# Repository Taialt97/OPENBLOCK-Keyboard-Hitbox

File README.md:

>:warning: This project is currently under development; the PCBs have not been tested and may require additional optimization.

# Introduction
This project aims to create an open-source, modular, and easy-to-understand design for a Hit Box layout using the Raspberry Pi (RP2040) as the core. My goal is to make the project as accessible and customizable as possible, providing everyone with the flexibility to adapt the design to their specific needs.

## Chip Compatibility
- **GP2040 chip**: Offers higher compatibility with PC, PS4, PS3, Switch, and Xbox.

| ProMicro (Mega32U4) | RespbarryPie (GP2040) | NameOfSwitch | Action      | PlayStation   | Xbox   |
|---------------------|-----------------------|--------------|-------------|---------------|----------------|
| 6                   | 6                     | MX10         | Up         | Dpad Up   | Dpad Up             |            |                |
| 14                  | 20                    | MX2          | Down        |Dpad Down   | Dpad Down           |            |                |
| 16                  | 23                    | MX1          | Left        | Dpad Left   | Dpad Left           |            |                |
| 15                  | 22                    | MX3          | Right       | Dpad Right       | Dpad Right          |            |                |
| 21                  | 29                    | MX4          | Light Punch | Square        | X              |            |                |
| 5                   | 5                     | MX11         | Light Kick  | X             | A              |            |                |
| 4                   | 4                     | MX5          | Medium Punch| Circle        | B              |            |                |
| 20                  | 28                    | MX12         | Medium Kick | Triangle      | Y              |            |                |
| 18                  | 26                    | MX6          | Heavy Punch | L1            | LB             |            |                |
| 19                  | 27                    | MX13         | Heavy Kick  | R1            | RB             |            |                |
| 2                   | 2                     | MX7          | Triple Punch| L2            | LT             |            |                |
| 3                   | 3                     | MX14         | Triple Kick | R2            | RT             |            |                |
| 8                   | 8                     | MX8          | Select 1    | Select        | Back           |            |                |
| 7                   | 7                     | MX9          | Select 2    | Start         | Start          |            |                |

# Costs
The cost to build the fight-stick will depend on parts, shipping, and tools. Below is a breakdown:

1. PCB (minimum order of 5) without shipping: **$8**. Shipping will vary by location and method.
2. Parts for PCB assembly: **$25** (hot swap sockets, keys, switches, Pro Micro, and IC Sockets).
3. Tools: Varies widely, but a cost-effective approach is possible.

## Part List
### Micro Chips List
Below is a list of top-tier microcontrollers that I've found to be the best in the market. While more cost-effective alternatives are available from sites like Aliexpress (which I've personally tested and found satisfactory), the following options are slightly more expensive but come with a guarantee of proper functionality.

If you're using a different 12-pin microcontroller that you think should be included here, feel free to leave a comment!

1. [Elite-Pi - USB-C Pro Micro Replacement RP2040 Controller](https://keeb.io/collections/diy-parts/products/elite-pi-usb-c-pro-micro-replacement-rp2040)
2. [SparkFun Pro Micro - RP2040](https://www.sparkfun.com/products/18288)

### Parts List
To ensure affordability, I've listed essential parts and some alternatives:

- PCB | $8 (without shipping)
- (optional) Hot-swappable PCB socket | $3
- Keycaps | $5-$15 (depends on quality)
- Switch | $5-$50 (depends on the manufacturer and "quality" of the switch)
- Pro Micro | $4-$30 (ensure the chip is **RP2040**)

### Recommended
- KESTER SOLDER | $35-$60 (quality soldering wire)
- PINECIL – Smart Mini Portable Soldering Iron (Version 2) | $25.99-$35.99

# Code

Upon connecting the microcontroller to your computer, a new drive will appear. 
- Drag the `nuke.h` file into this drive; the microcontroller will disconnect and then reconnect.
- Drag the `OpenBlock.h` file into the drive. You'll hear a sound indicating that the drive has disconnected and reconnected.

To test your controller, visit the [Gamepad Tester Website](https://hardwaretester.com/gamepad).
For modifying the code or creating new code, go to the [GP2040-CE](https://gp2040-ce.info/#/) website.
There, you'll find all the resources you need to customize or create new code. If you have any questions, refer to our [Discord channel](https://discord.gg/kJDAZVwU) — they're awesome!

# Note
This project is an open-source initiative, designed for modularity and ease of understanding. Contributions and suggestions from the community are welcome, fostering collaboration and growth.

# Sponsorship
This repository is sponsored by [PCBWay](https://www.pcbway.com/).

PCBWay specializes in manufacturing high-quality PCBs. They offer a range of services including PCB prototyping, assembly, and much more. We are grateful for their support in making this project possible.
Simplify Your Custom PCB Orders with PCBWay

Ordering custom PCBs has never been easier, thanks to PCBWay's intuitive platform. With the 'Instant Quote' feature, you can swiftly enter crucial information such as PCB type, dimensions, and material. Plus, helpful tooltips and guides are there to assist you every step of the way.
Unmatched Verification Process

What sets PCBWay apart is their meticulous verification process. Once you upload your Gerber files, a team of experts scrutinizes them for any errors or omissions. You'll be promptly notified of any issues via email or directly on the platform, ensuring a nearly error-free process.
Real-Time Project Tracking

PCBWay takes your experience up a notch by offering real-time project tracking. This level of transparency allows you to better manage your project timelines and make well-informed decisions.
Reliable and Fast Shipping

When it's time to ship, PCBWay provides trustworthy options like DHL, FedEx, and OCS. Need it fast? Expedited shipping is available right from the get-go. In a recent test run, the entire process—from uploading the Gerber files to receiving the finished PCBs—took just six days.
Conclusion

PCBWay is a top choice for anyone transitioning from generic to custom PCBs. The platform excels in ease of use, quality control, and speed, making it ideal for specialized projects.
For more information, visit their [website](https://www.pcbway.com/).

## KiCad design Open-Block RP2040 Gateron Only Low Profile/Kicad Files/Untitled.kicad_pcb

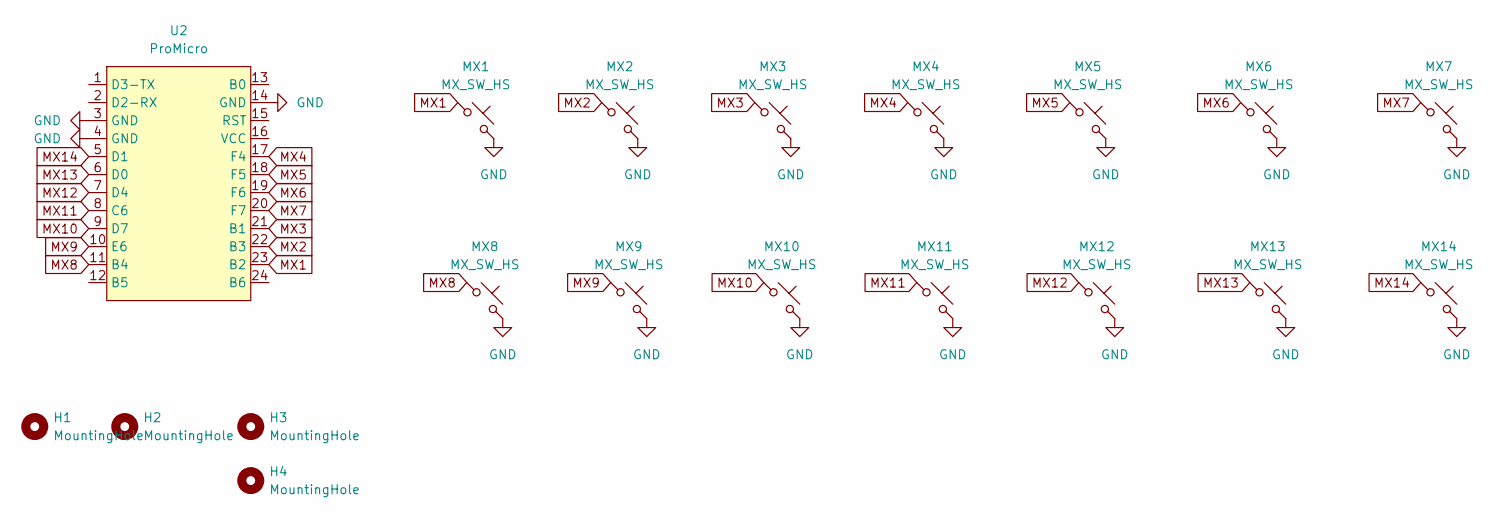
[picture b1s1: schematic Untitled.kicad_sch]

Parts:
H1, H2, H3, H4: MountingHole; MountingHole_2.2mm_M2_DIN965_Pad
MX1, MX2, MX3, MX4, MX5, MX6, MX7, MX8, MX9, MX10, MX11, MX12, MX13, MX14: MX_SW_HS; KAILHCHOK_V2_GATERON_SW_HS_(KAILH)
U2: ProMicro; Elite-C_ACH

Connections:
GND: MX1.2, MX2.2, MX3.2, MX4.2, MX5.2, MX6.2, MX7.2, MX8.2, MX9.2, MX10.2, MX11.2, MX12.2, MX13.2, MX14.2, U2.3 (GND), U2.4 (GND), U2.14 (GND)
MX1: MX1.1, U2.23 (B2)
MX2: MX2.1, U2.22 (B3)
MX3: MX3.1, U2.21 (B1)
MX4: MX4.1, U2.17 (F4)
MX5: MX5.1, U2.18 (F5)
MX6: MX6.1, U2.19 (F6)
MX7: MX7.1, U2.20 (F7)
MX8: MX8.1, U2.11 (B4)
MX9: MX9.1, U2.10 (E6)
MX10: MX10.1, U2.9 (D7)
MX11: MX11.1, U2.8 (C6)
MX12: MX12.1, U2.7 (D4)
MX13: MX13.1, U2.6 (D0)
MX14: MX14.1, U2.5 (D1)

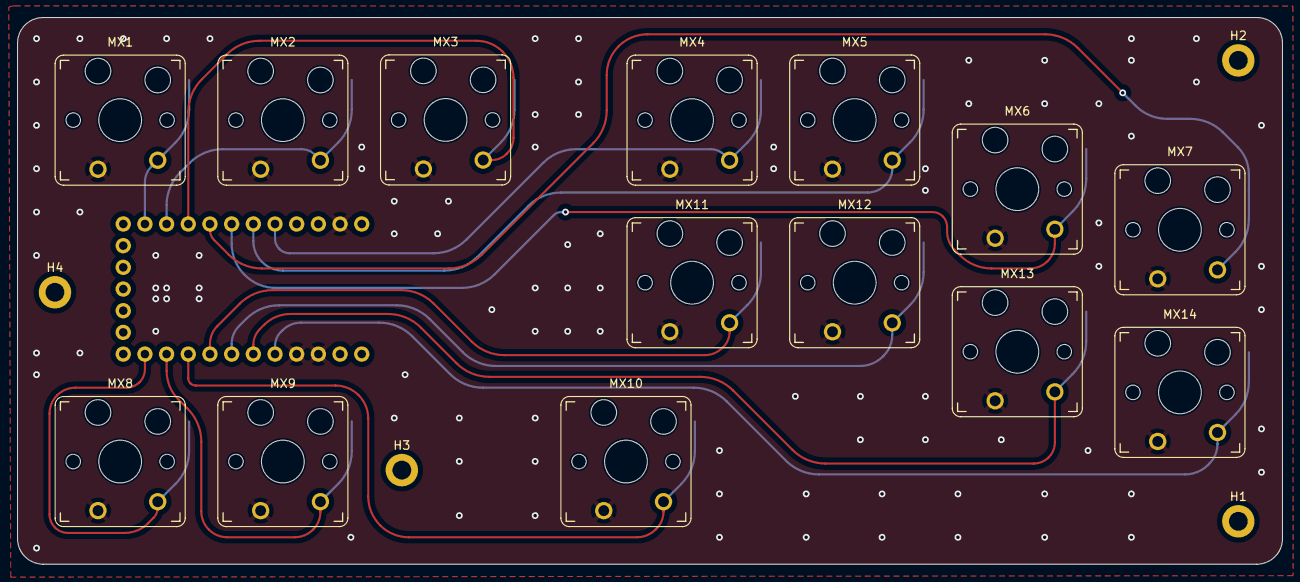
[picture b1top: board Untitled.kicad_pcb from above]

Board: 2 copper layers, 148.2 x 64.1 mm, 19 parts (1 on the bottom side), 15 nets.

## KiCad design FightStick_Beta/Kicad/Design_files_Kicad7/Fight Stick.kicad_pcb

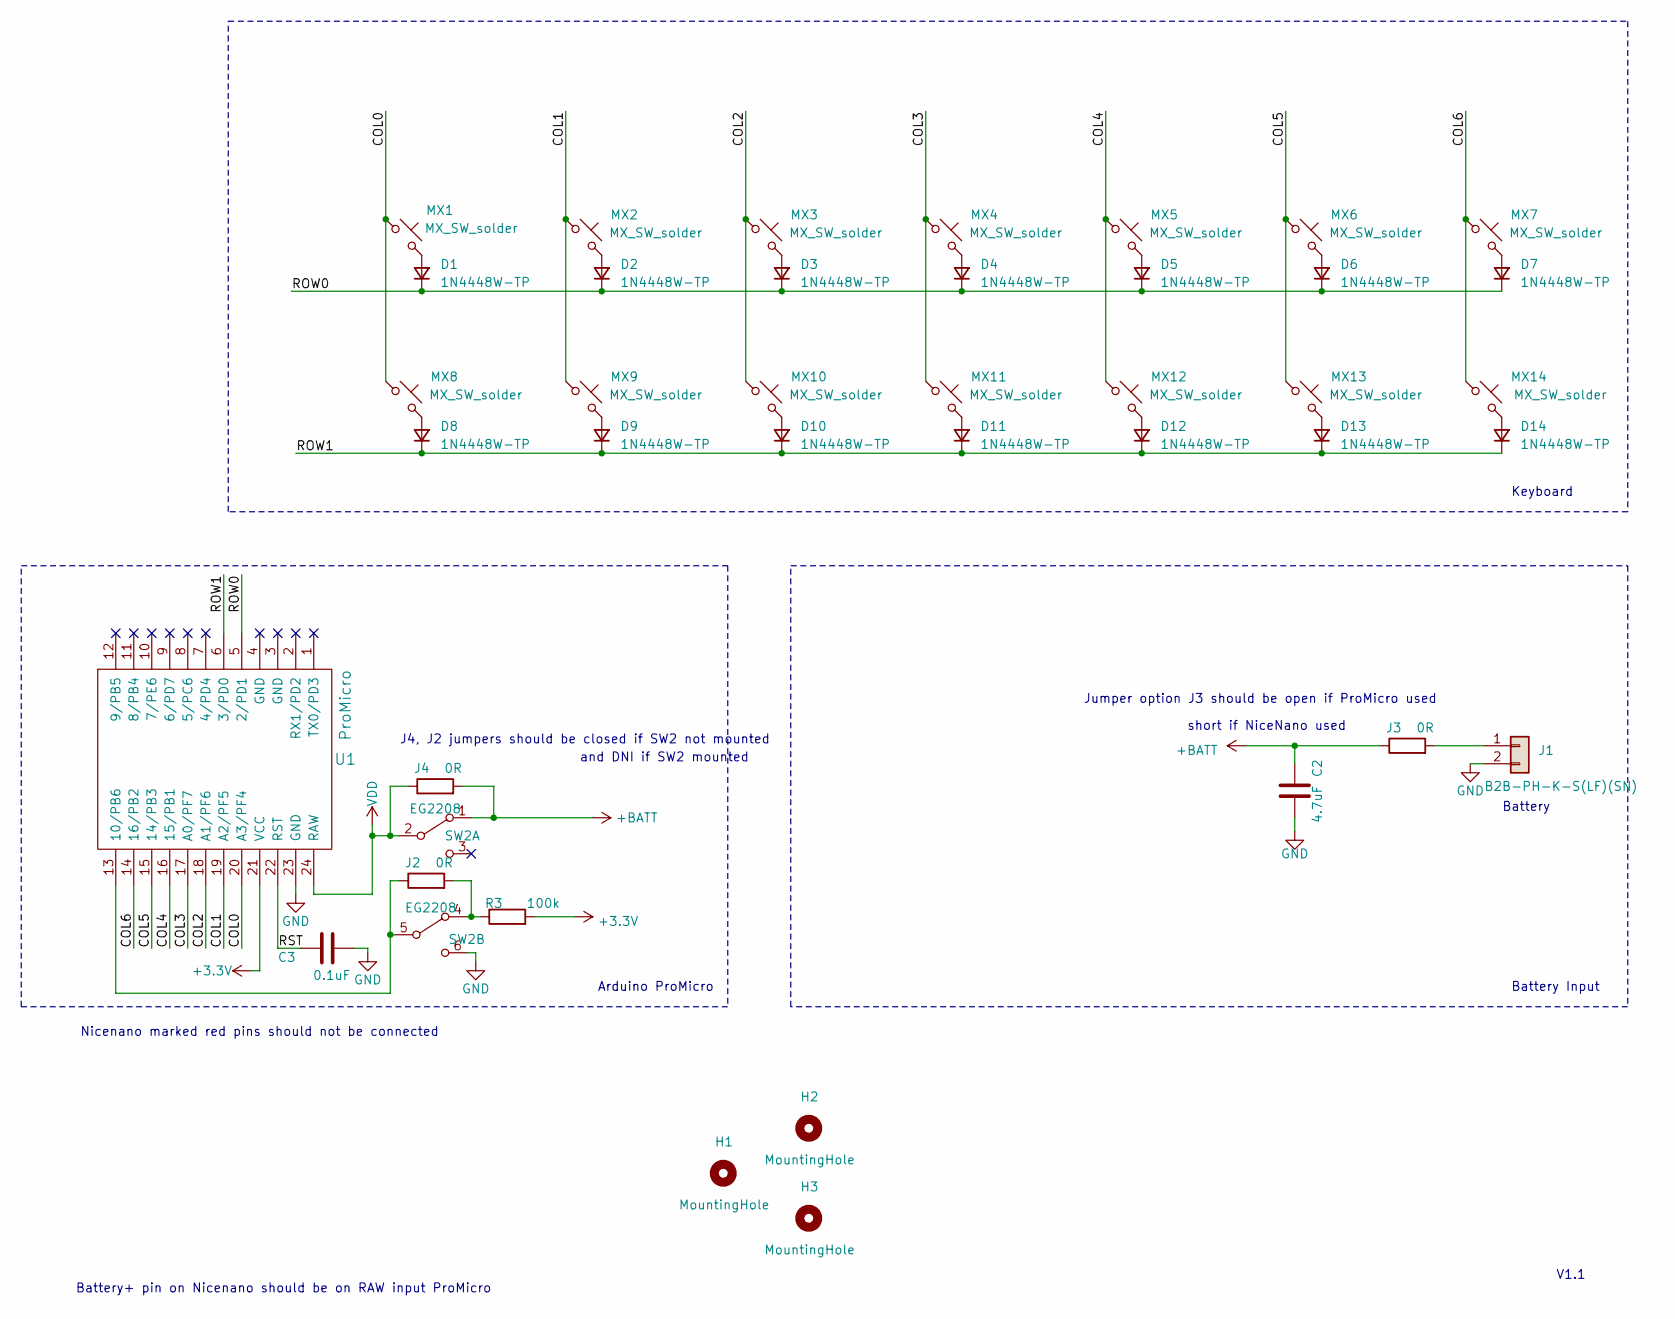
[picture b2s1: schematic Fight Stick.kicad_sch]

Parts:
C2: 4.7uF; C_0805_2012Metric; MPN CC0805ZRY5V6BB475; Digikey PN 311-1371-1-ND
C3: 0.1uF; C_0805_2012Metric; MPN CC0805ZRY5V6BB475; Digikey PN 311-1371-1-ND
D1, D2, D3, D4, D5, D6, D7, D8, D9, D10, D11, D12, D13, D14: 1N4448W-TP; D_SOD-123; MPN 1N4448W-TP; Digikey PN 1N4448WTPMSCT-ND
H1, H2, H3: MountingHole; MountingHole_4.3mm_M4
J1: B2B-PH-K-S(LF)(SN); JST_PH_B2B-PH-K_1x02_P2.00mm_Vertical; MPN B2B-PH-K-S(LF)(SN); Digikey PN 455-1704-ND
J2, J3, J4: 0R; R_0805_2012Metric; MPN RC0805FR-070RL; Digikey PN 311-0.0CRCT-ND
MX1, MX2, MX3, MX4, MX5, MX6, MX7, MX8, MX9, MX10, MX11, MX12, MX13, MX14: MX_SW_solder; Kailh_socket_MX_optional
R3: 100k; R_0805_2012Metric; MPN RC0805JR-07100KL; Digikey PN 311-100KARCT-ND
SW2: EG2208; SW_EG2208
U1: ProMicro; ArduinoProMicro

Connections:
+3.3V: R3.2, U1.21 (VCC)
+BATT: C2.1, J3.1, J4.2, SW2.1 (A)
/COL0: MX1.1, MX8.1, U1.20 (A3/PF4)
/COL1: MX2.1, MX9.1, U1.19 (A2/PF5)
/COL2: MX3.1, MX10.1, U1.18 (A1/PF6)
/COL3: MX4.1, MX11.1, U1.17 (A0/PF7)
/COL4: MX5.1, MX12.1, U1.16 (15/PB1)
/COL5: MX6.1, MX13.1, U1.15 (14/PB3)
/COL6: MX7.1, MX14.1, U1.14 (16/PB2)
/ROW0: D1.1 (K), D2.1 (K), D3.1 (K), D4.1 (K), D5.1 (K), D6.1 (K), D7.1 (K), U1.5 (2/PD1)
/ROW1: D8.1 (K), D9.1 (K), D10.1 (K), D11.1 (K), D12.1 (K), D13.1 (K), D14.1 (K), U1.6 (3/PD0)
/RST: C3.1, U1.22 (RST)
GND: C2.2, C3.2, J1.2, SW2.6 (C), U1.23 (GND)
unnamed: D1.2 (A), MX1.2
unnamed: D2.2 (A), MX2.2
unnamed: D3.2 (A), MX3.2
unnamed: D4.2 (A), MX4.2
unnamed: D5.2 (A), MX5.2
unnamed: D6.2 (A), MX6.2
unnamed: D7.2 (A), MX7.2
unnamed: D8.2 (A), MX8.2
unnamed: D9.2 (A), MX9.2
unnamed: D10.2 (A), MX10.2
unnamed: D11.2 (A), MX11.2
unnamed: D12.2 (A), MX12.2
unnamed: D13.2 (A), MX13.2
unnamed: D14.2 (A), MX14.2
unnamed: J1.1, J3.2
unnamed: J2.2, R3.1, SW2.4 (A)
unnamed: J2.1, SW2.5 (B), U1.13 (10/PB6)
VDD: J4.1, SW2.2 (B), U1.24 (RAW)

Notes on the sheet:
Battery
Keyboard
Battery Input
Battery+ pin on Nicenano should be on RAW input ProMicro
V1.1
and DNI if SW2 mounted
Arduino ProMicro
J4, J2 jumpers should be closed if SW2 not mounted
Jumper option J3 should be open if ProMicro used
Nicenano marked red pins should not be connected
short if NiceNano used

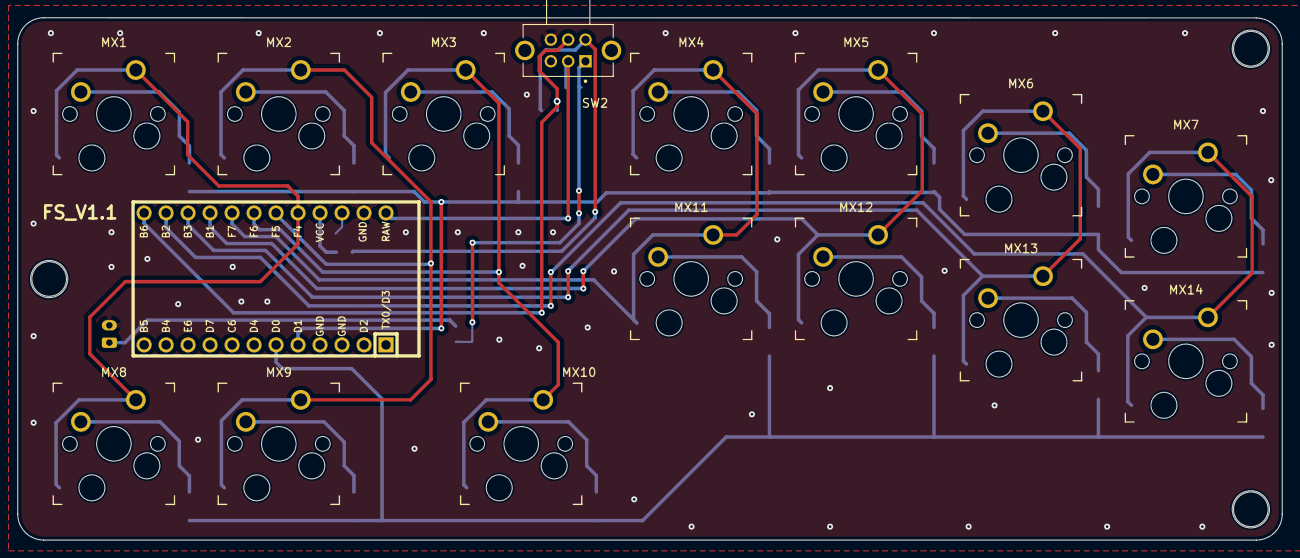
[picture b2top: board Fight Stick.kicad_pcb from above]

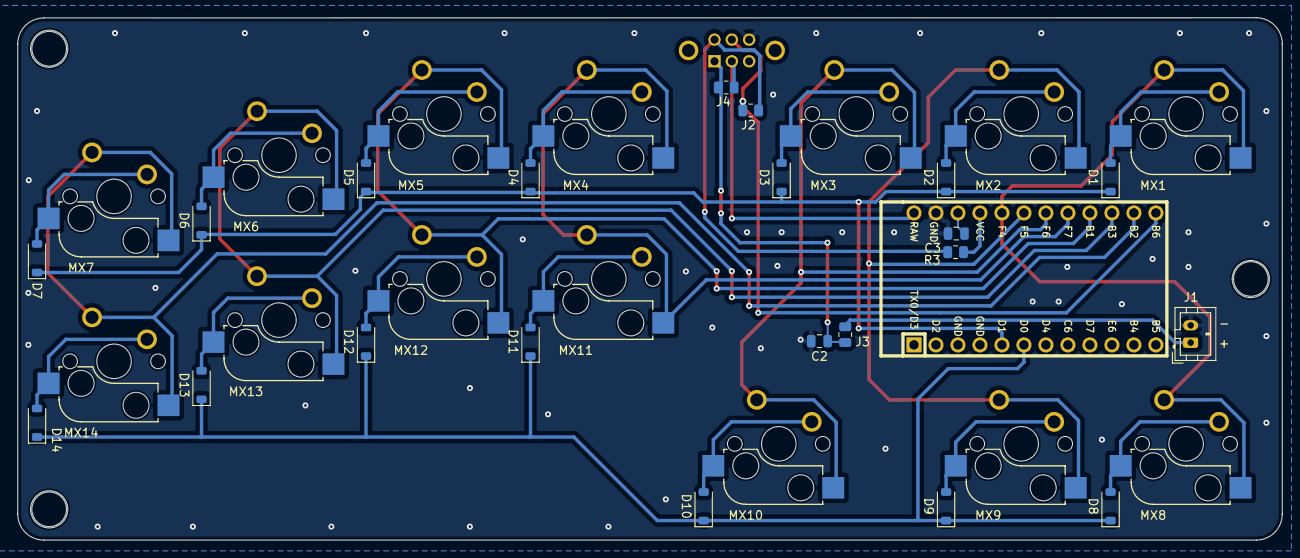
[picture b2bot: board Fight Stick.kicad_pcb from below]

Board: 2 copper layers, 146.1 x 60.3 mm, 40 parts (22 on the bottom side), 31 nets.

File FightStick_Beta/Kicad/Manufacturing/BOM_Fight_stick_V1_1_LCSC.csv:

Designator,Footprint,Quantity,Value, Part #,LCSC Part #
C2,805,1,4.7uF,CC0805KKX7R8BB475,C354262
C3,805,1,0.1uF,CC0805KRX7R9BB104,C49678
"D1, D10, D11, D12, D13, D14, D2, D3, D4, D5, D6, D7, D8, D9",D_SOD-123,14,1N4448W-TP,1N4448W-TP,C668855
J1,JST_PH_B2B-PH-K_1x02_P2.00mm_Vertical,1,B2B-PH-K-S(LF)(SN),B2B-PH-K-S(LF)(SN),C131337
"MX1, MX10, MX11, MX12, MX13, MX14, MX2, MX3, MX4, MX5, MX6, MX7, MX8, MX9",Kailh_socket_MX_optional,14,MX_SW_solder,Kailh CPG151101D212 ,C400234
R3,805,1,100k,RC0805FR-07100KL,C96346
SW2,SW_EG2208,1,EG2208,,C609827 
U1,ArduinoProMicro,1,ProMicro,custom module,

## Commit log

2023-06-02 Uploaded Files
2023-06-03 Added Fusion 360 Files
2023-08-10 fight stick 2 direct
2023-08-11 second version upload
2023-08-12 Version 2
2023-08-25 lowprofile
2023-08-25 update RM
2023-08-26 Create LICENSE

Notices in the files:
README.md:
License: MIT
